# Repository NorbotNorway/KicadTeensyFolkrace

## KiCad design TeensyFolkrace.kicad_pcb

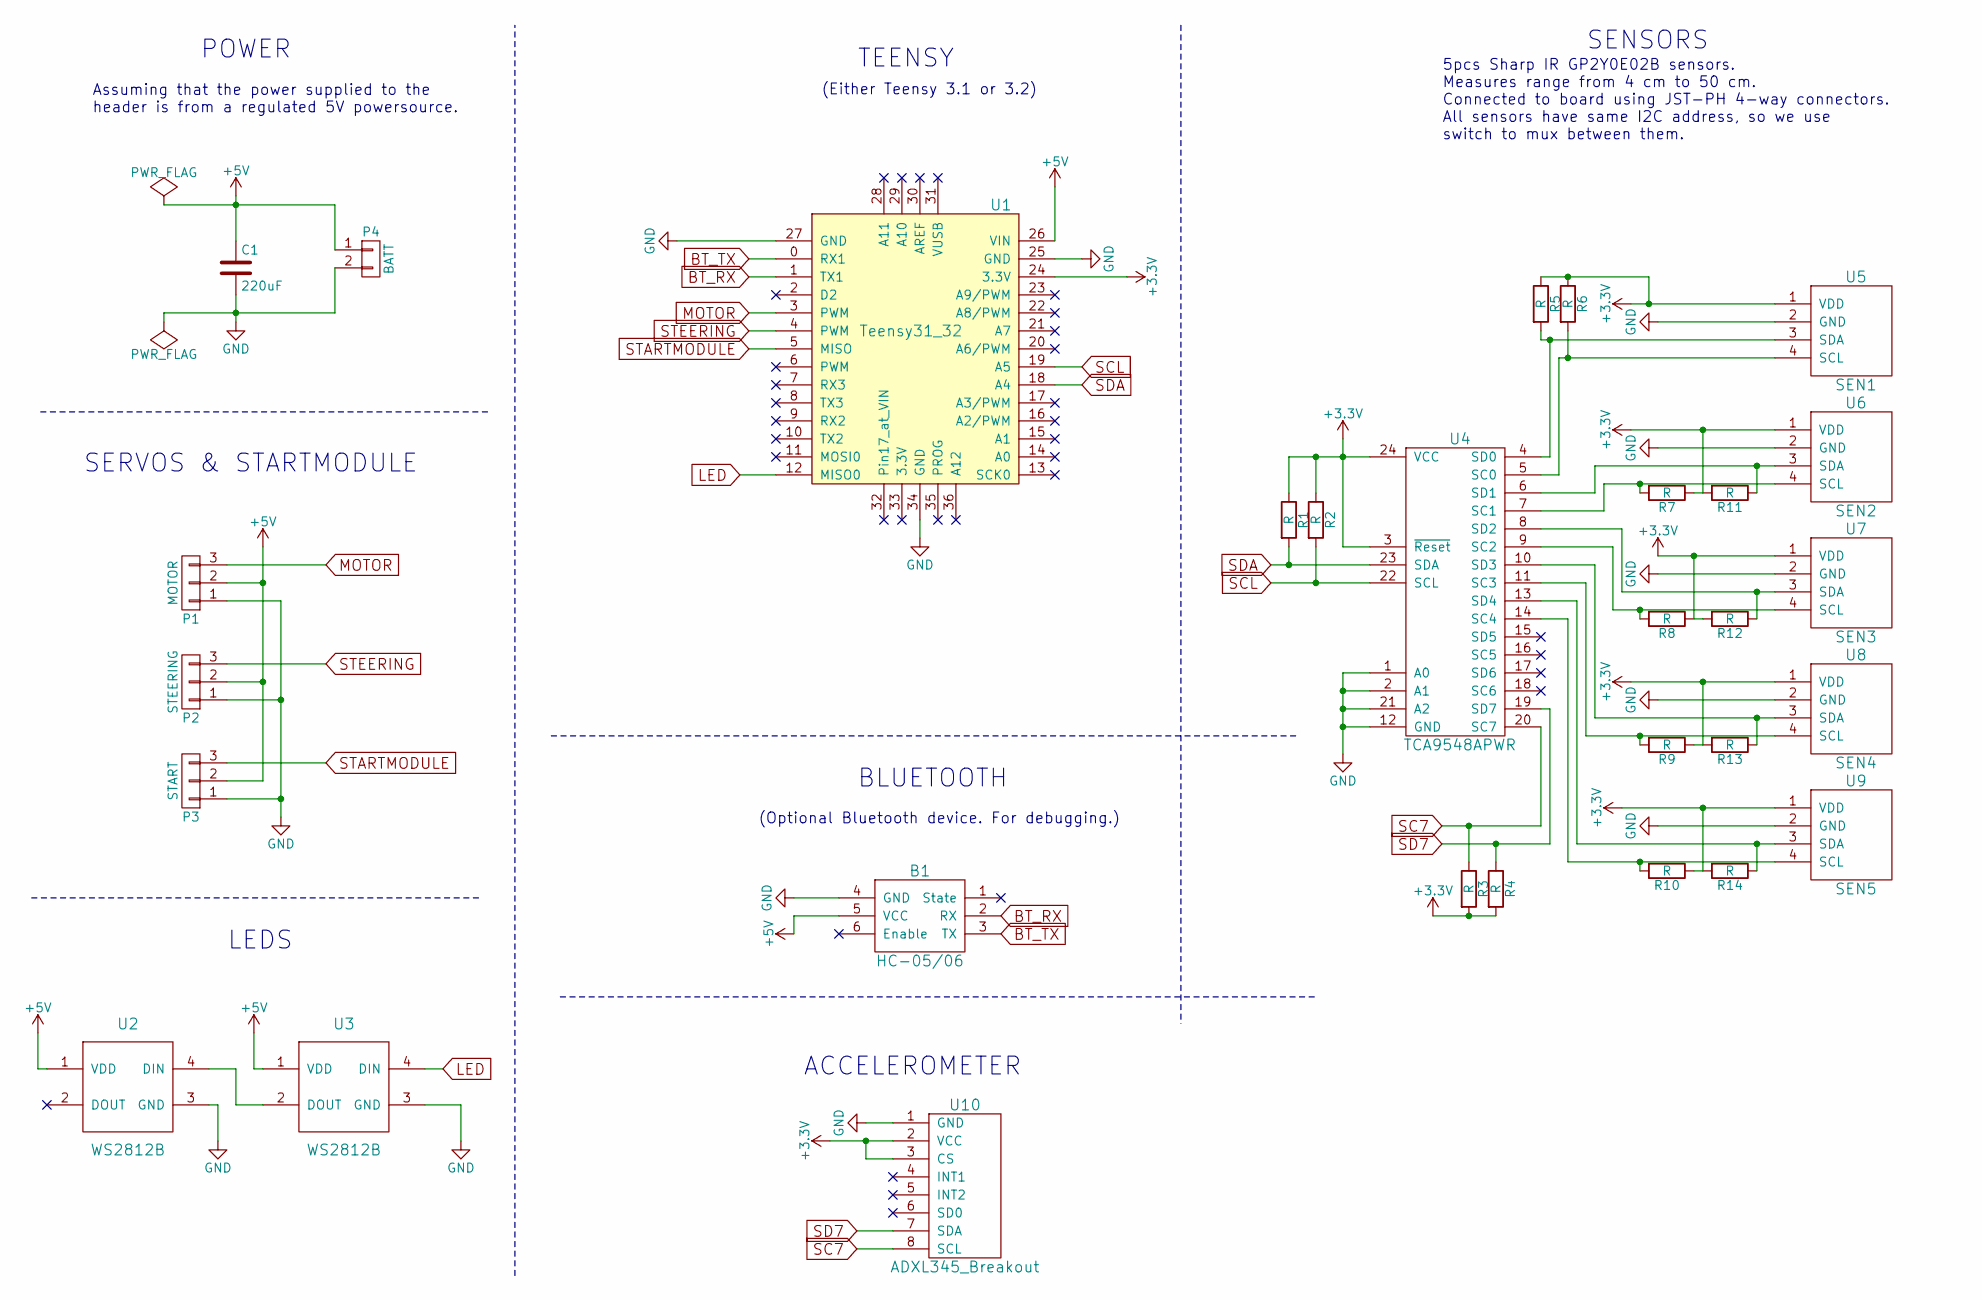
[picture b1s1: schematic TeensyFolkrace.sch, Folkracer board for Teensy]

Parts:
B1: HC-05/06; Pin_Header_Straight_1x06
C1: 220uF; C_0603_HandSoldering
P1: MOTOR; Pin_Header_Straight_1x03
P2: STEERING; Pin_Header_Straight_1x03
P3: START; Pin_Header_Straight_1x03
P4: BATT; Pin_Header_Straight_1x02
R1, R2, R3, R4, R5, R6, R7, R8, R9, R10, R11, R12, R13, R14: R; R_0603_HandSoldering
U1: Teensy31_32
U2, U3: WS2812B
U4: TCA9548APWR; TSSOP-24_4.4x7.8mm_Pitch0.65mm
U5: SEN1; Pin_Header_Straight_1x04
U6: SEN2; Pin_Header_Straight_1x04
U7: SEN3; Pin_Header_Straight_1x04
U8: SEN4; Pin_Header_Straight_1x04
U9: SEN5; Pin_Header_Straight_1x04
U10: ADXL345_Breakout; Pin_Header_Straight_1x08

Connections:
+3V3: R1.1, R2.1, R3.2, R4.2, R5.1, R6.1, R7.1, R8.1, R9.1, R10.1, R11.2, R12.2, R13.2, R14.2, U1.24 (3.3V), U4.3 (~Reset), U4.24 (VCC), U5.1 (VDD), U6.1 (VDD), U7.1 (VDD), U8.1 (VDD), U9.1 (VDD), U10.2 (VCC), U10.3 (CS)
+5V: B1.5 (VCC), C1.1, P1.2, P2.2, P3.2, P4.1, U1.26 (VIN), U2.1 (VDD), U3.1 (VDD)
BT_RX: B1.2 (RX), U1.1 (TX1)
BT_TX: B1.3 (TX), U1.0 (RX1)
GND: B1.4 (GND), C1.2, P1.1, P2.1, P3.1, P4.2, U1.25 (GND), U1.27 (GND), U1.34 (GND), U2.3 (GND), U3.3 (GND), U4.1 (A0), U4.2 (A1), U4.12 (GND), U4.21 (A2), U5.2 (GND), U6.2 (GND), U7.2 (GND), U8.2 (GND), U9.2 (GND), U10.1 (GND)
LED: U1.12 (MISO0), U3.4 (DIN)
MOTOR: P1.3, U1.3 (PWM)
unnamed: R5.2, U4.4 (SD0), U5.3 (SDA)
unnamed: R6.2, U4.5 (SC0), U5.4 (SCL)
unnamed: R7.2, U4.7 (SC1), U6.4 (SCL)
unnamed: R8.2, U4.9 (SC2), U7.4 (SCL)
unnamed: R9.2, U4.11 (SC3), U8.4 (SCL)
unnamed: R10.2, U4.14 (SC4), U9.4 (SCL)
unnamed: R11.1, U4.6 (SD1), U6.3 (SDA)
unnamed: R12.1, U4.8 (SD2), U7.3 (SDA)
unnamed: R13.1, U4.10 (SD3), U8.3 (SDA)
unnamed: R14.1, U4.13 (SD4), U9.3 (SDA)
unnamed: U2.4 (DIN), U3.2 (DOUT)
SC7: R3.1, U4.20 (SC7), U10.8 (SCL)
SCL: R2.2, U1.19 (A5), U4.22 (SCL)
SD7: R4.1, U4.19 (SD7), U10.7 (SDA)
SDA: R1.2, U1.18 (A4), U4.23 (SDA)
STARTMODULE: P3.3, U1.5 (MISO)
STEERING: P2.3, U1.4 (PWM)

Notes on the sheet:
TEENSY
BLUETOOTH
SENSORS
POWER
SERVOS & STARTMODULE
LEDS
(Optional Bluetooth device. For debugging.)
5pcs Sharp IR GP2Y0E02B sensors. Measures range from 4 cm to 50 cm. Connected to board using JST-PH 4-way connectors. All sensors have same I2C address, so we use switch to mux between them.
(Either Teensy 3.1 or 3.2)
ACCELEROMETER
Assuming that the power supplied to the header is from a regulated 5V powersource.

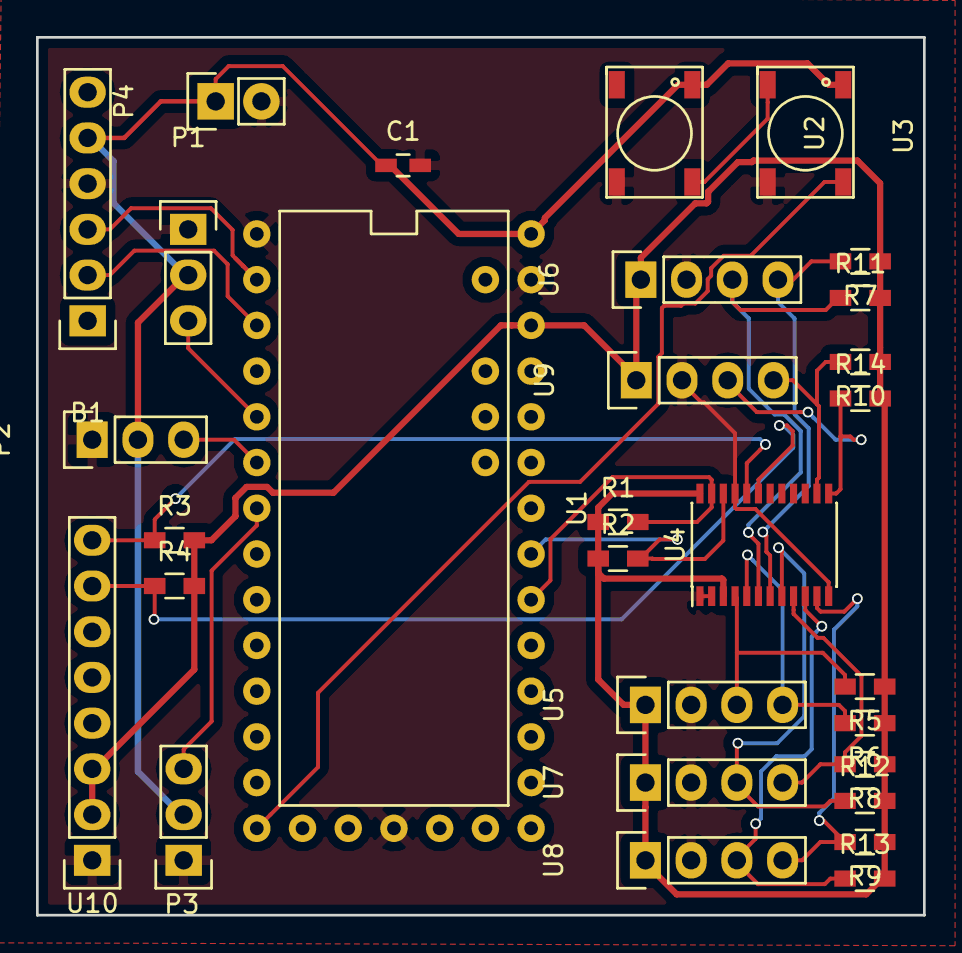
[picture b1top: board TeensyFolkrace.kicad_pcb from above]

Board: 2 copper layers, 49.3 x 48.8 mm, 30 parts (0 on the bottom side), 24 nets.

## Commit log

2016-01-19 Fixed hardcoded absolute path
2016-01-19 Added reset-resistor, and generated gerbers
